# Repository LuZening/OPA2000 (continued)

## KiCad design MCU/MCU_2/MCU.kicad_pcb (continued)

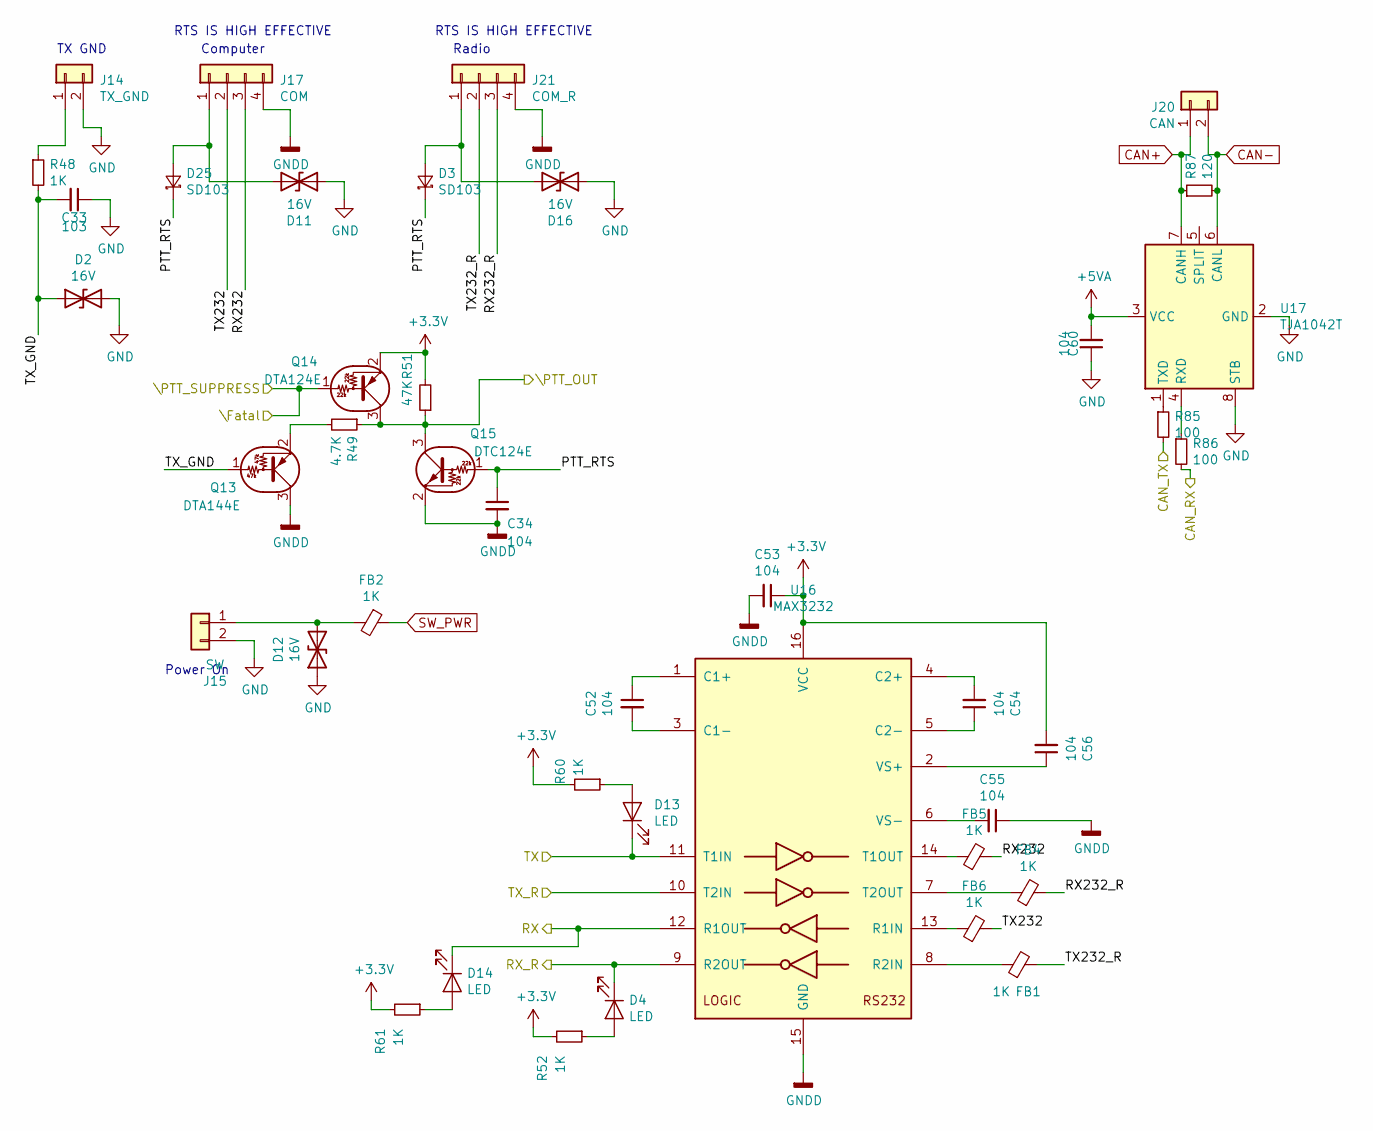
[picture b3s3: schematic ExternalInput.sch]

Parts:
C33: 103; 0805_C
C34, C52, C53, C54, C55, C56, C60: 104; 0805_C
D2, D11, D12, D16: 16V; SMA(DO-214AC)_S4
D3, D25: SD103; SOD-123
D4, D13, D14: LED; 0805_LED_S1
FB1, FB2, FB4, FB5, FB6: 1K; 0805_R
J14: TX_GND; PinHeader_1x02_P2.54mm_Vertical
J15: SW; PinHeader_1x02_P2.54mm_Vertical
J17: COM; JST_PH_B4B-PH-SM4-TB_1x04-1MP_P2.00mm_Vertical
J20: CAN; PinHeader_1x02_P2.54mm_Vertical
J21: COM_R; JST_PH_B4B-PH-SM4-TB_1x04-1MP_P2.00mm_Vertical
Q13: DTA144E; SOT-23(SOT-23-3)
Q14: DTA124E; SOT-23(SOT-23-3)
Q15: DTC124E; SOT-23(SOT-23-3)
R48, R52, R60, R61: 1K; 0805_R
R49: 4.7K; 0805_R
R51: 47K; 0805_R
R85, R86: 100; 0805_R
R87: 120; 0805_R
U16: MAX3232; SOIC-16_150MIL
U17: TJA1042T; SOIC-8_150MIL

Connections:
+3V3: C53.1, C56.2, Q14.2 (E), R51.2, R52.2, R60.2, R61.2, U16.16 (VCC); also elsewhere on the board
/CAN_RX: R86.2; also elsewhere on the board
/CAN_TX: R85.2; also elsewhere on the board
/ExternalInput/PTT_RTS: C34.1, D3.2 (K), D25.2 (K), Q15.1 (B)
/ExternalInput/RX232: FB5.2, J17.3
/ExternalInput/RX232_R: FB4.2, J21.3
/ExternalInput/TX232: FB6.2, J17.2
/ExternalInput/TX232_R: FB1.2, J21.2
/ExternalInput/TX_GND: C33.2, D2.1 (A1), Q13.1 (B), R48.2
/RX: D14.K, U16.12 (R1OUT); also elsewhere on the board
/RX3: D4.K, U16.9 (R2OUT); also elsewhere on the board
/TX: D13.K, U16.11 (T1IN); also elsewhere on the board
/TX3: U16.10 (T2IN); also elsewhere on the board
CAN+: J20.1, R87.1, U17.7 (CANH)
CAN-: J20.2, R87.2, U17.6 (CANL)
GND: C33.1, C34.2, C53.2, C55.1, C60.1, D2.2 (A2), D11.1 (A1), D12.1 (A1), D16.1 (A1), J14.2, J15.2, J17.4, J21.4, Q13.3 (C), Q15.2 (E), U16.15 (GND), U17.2 (GND), U17.8 (STB); also elsewhere on the board
unnamed: C52.1, U16.1 (C1+)
unnamed: C52.2, U16.3 (C1-)
unnamed: C54.1, U16.5 (C2-)
unnamed: C54.2, U16.4 (C2+)
unnamed: C55.2, U16.6 (VS-)
unnamed: C56.1, U16.2 (VS+)
unnamed: D4.A, R52.1
unnamed: D11.2 (A2), D25.1 (A), J17.1
unnamed: D12.2 (A2), FB2.2, J15.1
unnamed: D13.A, R60.1
unnamed: D14.A, R61.1
unnamed: D3.1 (A), D16.2 (A2), J21.1
unnamed: FB1.1, U16.8 (R2IN)
unnamed: FB4.1, U16.7 (T2OUT)
unnamed: FB5.1, U16.14 (T1OUT)
unnamed: FB6.1, U16.13 (R1IN)
unnamed: J14.1, R48.1
unnamed: Q13.2 (E), R49.2
unnamed: R85.1, U17.1 (TXD)
unnamed: R86.1, U17.4 (RXD)
SW_PWR: FB2.1
\Fatal: Q14.1 (B); also elsewhere on the board
\PTT: Q14.3 (C), Q15.3 (C), R49.1, R51.1; also elsewhere on the board

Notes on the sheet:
Power On
TX GND
Computer
RTS IS HIGH EFFECTIVE
Radio

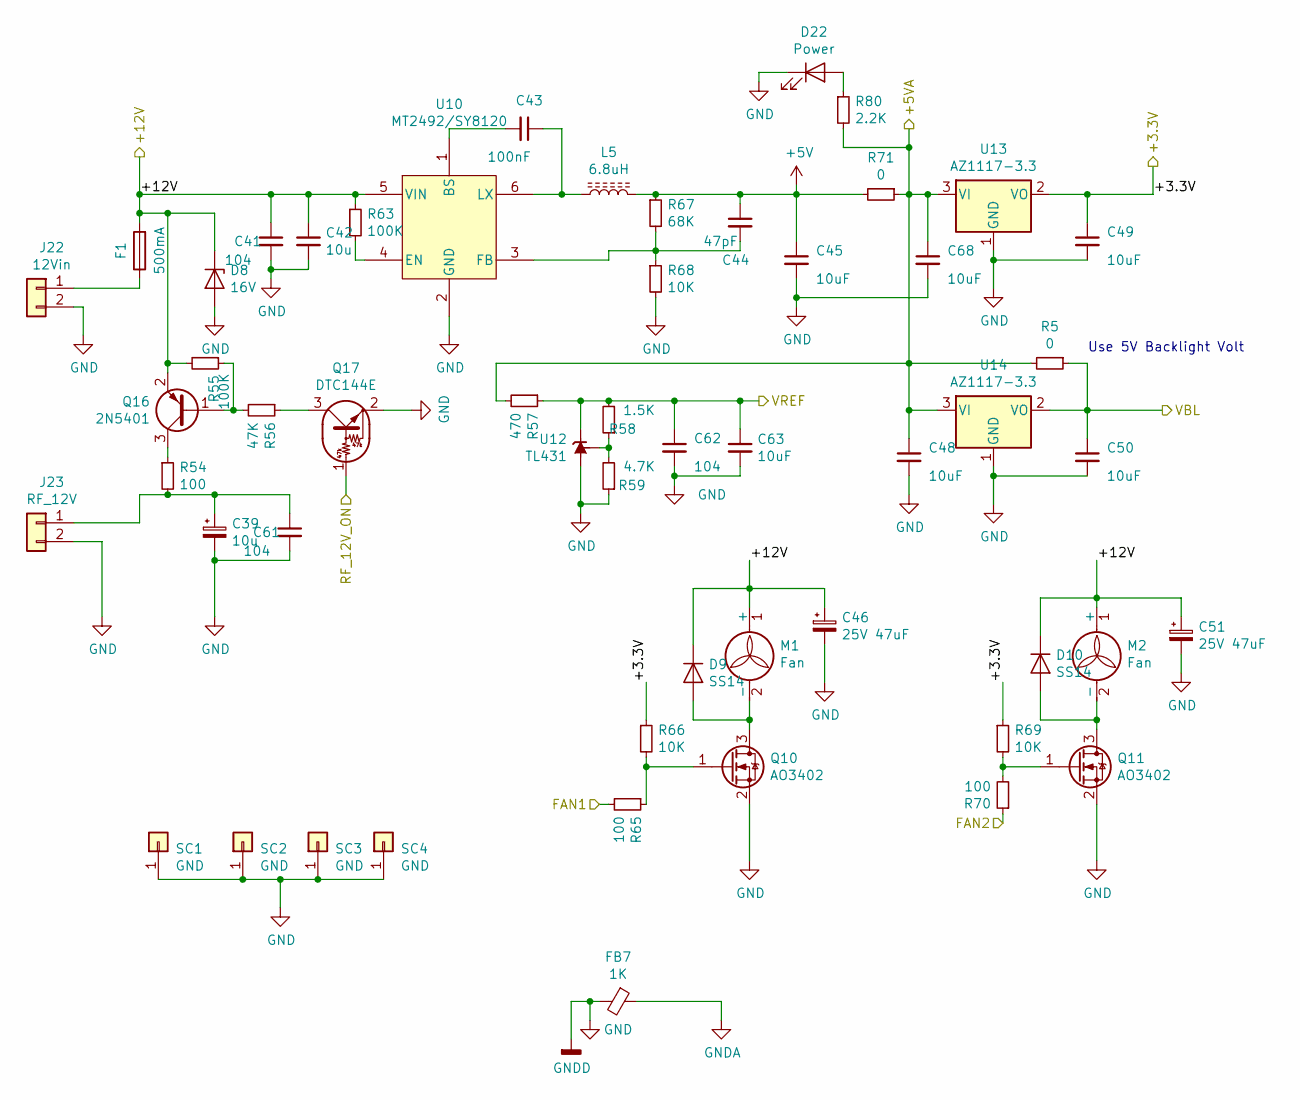
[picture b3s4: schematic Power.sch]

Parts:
C39: 10u; CP_Radial_D5.0mm_P2.50mm
C41, C61, C62: 104; 0805_C
C42: 10u; 0805_C
C43: 100nF; 0805_C
C44: 47pF; 0805_C
C45, C48, C49, C50, C63, C68: 10uF; 0805_C
C46, C51: 25V 47uF; CP_Radial_D5.0mm_P2.50mm
D8: 16V; LL-34
D9, D10: SS14; SMA(DO-214AC)_S1
D22: Power; 0805_LED_S1
F1: 500mA; 1206_R
FB7: 1K; 0201_R
J22: 12Vin; JST_PH_B2B-PH-SM4-TB_1x02-1MP_P2.00mm_Vertical
J23: RF_12V; JST_PH_B2B-PH-SM4-TB_1x02-1MP_P2.00mm_Vertical
L5: 6.8uH; L_SMD4030_hand
M1, M2: Fan; JST_PH_B2B-PH-SM4-TB_1x02-1MP_P2.00mm_Vertical
Q10, Q11: AO3402; SOT-23(SOT-23-3)
Q16: 2N5401; SOT-23(SOT-23-3)
Q17: DTC144E; SOT-23(SOT-23-3)
R5: 0; 0603_R
R54, R65, R70: 100; 0805_R
R55, R63: 100K; 0805_R
R56: 47K; 0805_R
R57: 470; 0805_R
R58: 1.5K; 0805_R
R59: 4.7K; 0805_R
R66, R68, R69: 10K; 0805_R
R67: 68K; 0805_R
R71: 0; 1206_R
R80: 2.2K; 0805_R
SC1, SC2, SC3, SC4: GND; M3_Screwhole
U10: MT2492/SY8120; SOT-23-6
U12: TL431; SOT-23(SOT-23-3)
U13, U14: AZ1117-3.3; SOT-223

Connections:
+3V3: C49.1, R66.1, R69.1, U13.2 (VO); also elsewhere on the board
+5V: C44.1, C45.1, L5.2, R67.1, R71.2
+12V: C41.1, C42.1, C46.1, C51.1, D8.2 (K), D9.2 (K), D10.2 (K), F1.2, M1.1 (+), M2.1 (+), Q16.2 (E), R55.2, R63.1, U10.5 (VIN); also elsewhere on the board
FAN1: R65.2; also elsewhere on the board
FAN2: R70.1; also elsewhere on the board
GND: C39.2, C41.2, C42.2, C45.2, C46.2, C48.2, C49.2, C50.2, C51.2, C61.2, C62.2, C63.2, C68.2, D8.1 (A), D22.K, FB7.2, J22.2, J23.2, Q10.2 (S), Q11.2 (S), Q17.2 (E), R59.1, R68.2, SC1.1, SC2.1, SC3.1, SC4.1, U10.2 (GND), U12.3 (A), U12.6 (A), U12.7 (A), U13.1 (GND), U14.1 (GND); also elsewhere on the board
GNDA: FB7.1; also elsewhere on the board
unnamed: C39.1, C61.1, J23.1, R54.2
unnamed: C43.1, L5.1, U10.6 (LX)
unnamed: C43.2, U10.1 (BS)
unnamed: C44.2, R67.2, R68.1, U10.3 (FB)
unnamed: D9.1 (A), M1.2 (-), Q10.3 (D)
unnamed: D10.1 (A), M2.2 (-), Q11.3 (D)
unnamed: D22.A, R80.1
unnamed: F1.1, J22.1
unnamed: Q10.1 (G), R65.1, R66.2
unnamed: Q11.1 (G), R69.2, R70.2
unnamed: Q16.1 (B), R55.1, R56.2
unnamed: Q16.3 (C), R54.1
unnamed: Q17.3 (C), R56.1
unnamed: R58.1, R59.2, U12.1 (REF)
unnamed: R63.2, U10.4 (EN)
RF_12V_ON: Q17.1 (B)
VBL: C50.1, R5.1, U14.2 (VO); also elsewhere on the board
VREF: C62.1, C63.1, R57.1, R58.2, U12.2 (K); also elsewhere on the board

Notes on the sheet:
Use 5V Backlight Volt

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
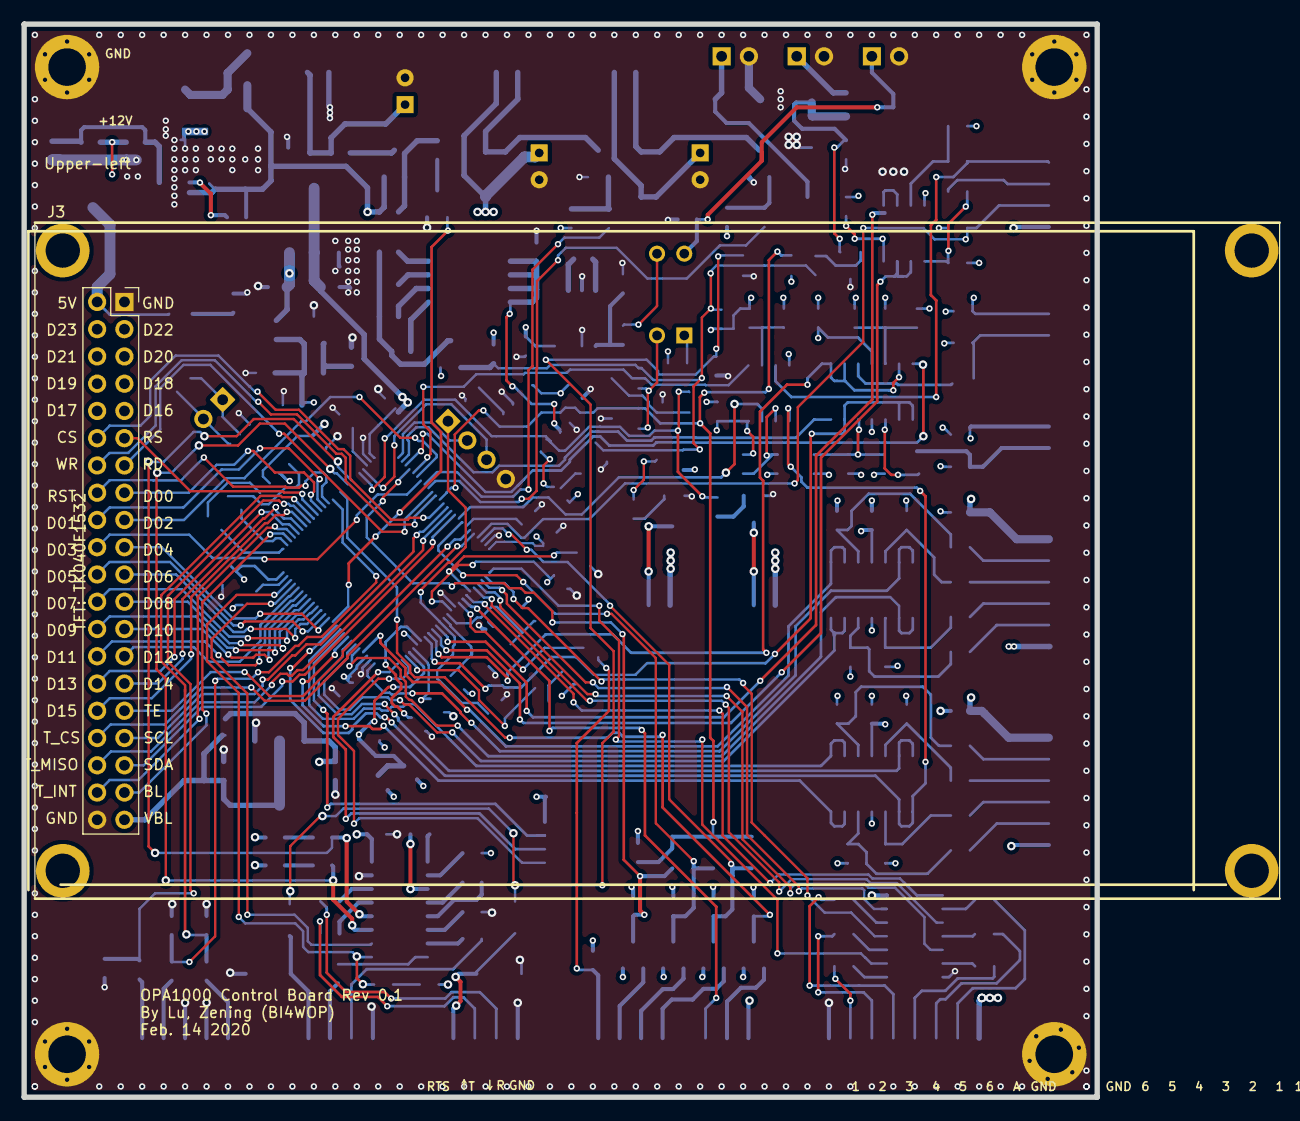
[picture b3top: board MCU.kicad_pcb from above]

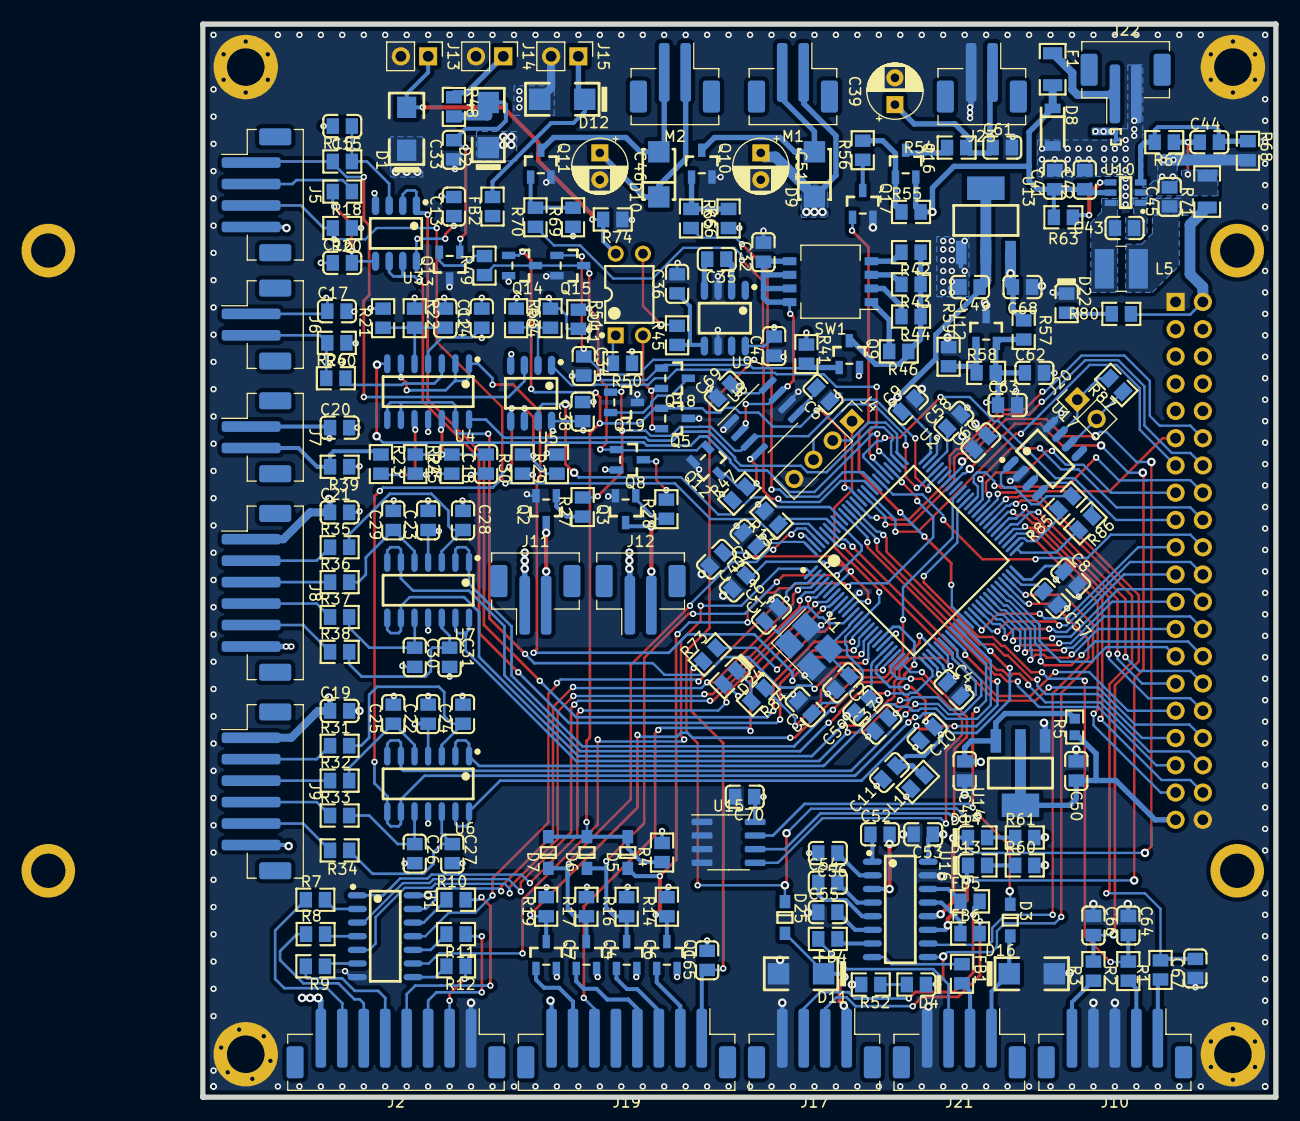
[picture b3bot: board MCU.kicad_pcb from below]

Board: 4 copper layers, 100.0 x 100.0 mm, 237 parts (236 on the bottom side), 205 nets.

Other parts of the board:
C5, C47, C69: 104; 0805_C
C32: 1uF; 0805_C
C35, C36: 10uF; 0805_C
D1: 16V; SMAF_S4
J11: In Relay; JST_PH_B2B-PH-SM4-TB_1x02-1MP_P2.00mm_Vertical
J12: Out Relay; JST_PH_B2B-PH-SM4-TB_1x02-1MP_P2.00mm_Vertical
J13: ALC out; PinHeader_1x02_P2.54mm_Vertical
Q2, Q3: 8050; SOT-23(SOT-23-3)
Q5, Q8, Q9, Q18, Q19: DTA144E; SOT-23(SOT-23-3)
Q12: DTC144E; SOT-23(SOT-23-3)
R27, R28, R41, R74: 10K; 0805_R
R42, R43, R44, R46: 51K; 0805_R
R45: 1K; 0805_R
R47: 100K; 0805_R
R50: 220; 0805_R
SW1: SW_DIP_x04; SW_DIP_SPSTx04_Slide_KingTek_DSHP04TS_W7.62mm_P1.27mm
U8: TLC555xD; SOIC-8_3.9x4.9mm_P1.27mm
U9: ICL7660; SOIC-8_150MIL
U11: PC817; DIP-4

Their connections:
+3V3: C47.2, C69.2, Q8.2, Q9.2, R41.1, R47.1, R50.1, U8.8, U9.8; also elsewhere on the board
+12V: J11.1, J12.1; also elsewhere on the board
/OutputSignals/REL_IN: J11.2, Q2.3
/OutputSignals/REL_OUT: J12.2, Q3.3
ALC: D1.1, J13.1, R74.2, U11.4
GND: C5.1, C32.2, C36.1, C47.1, C69.1, D1.2, J13.2, Q2.2, Q3.2, Q5.3, Q12.2, Q19.3, R74.1, U8.1, U8.6, U9.3, U9.6; also elsewhere on the board
unnamed: C5.2, U8.5
unnamed: C32.1, SW1.5, SW1.6, SW1.7, SW1.8, U8.2, U8.7
unnamed: C35.1, U9.2
unnamed: C35.2, U9.4
unnamed: C36.2, R45.2, U9.5
unnamed: Q2.1, R27.1
unnamed: Q3.1, R28.1
unnamed: Q8.3, R28.2
unnamed: Q9.3, R42.1, R43.1, R44.1, R46.1
unnamed: Q12.3, R47.2, U8.4
unnamed: Q5.2, Q18.2, U11.2
unnamed: Q18.3, Q19.2
unnamed: R42.2, SW1.4
unnamed: R43.2, SW1.3
unnamed: R44.2, SW1.2
unnamed: R45.1, U11.3
unnamed: R46.2, SW1.1
unnamed: R50.2, U11.1
Transmit: Q19.1, R27.2, U8.3; also elsewhere on the board
\Fatal: Q5.1; also elsewhere on the board
\PTT: Q8.1, Q9.1, Q12.1, Q18.1, R41.2; also elsewhere on the board

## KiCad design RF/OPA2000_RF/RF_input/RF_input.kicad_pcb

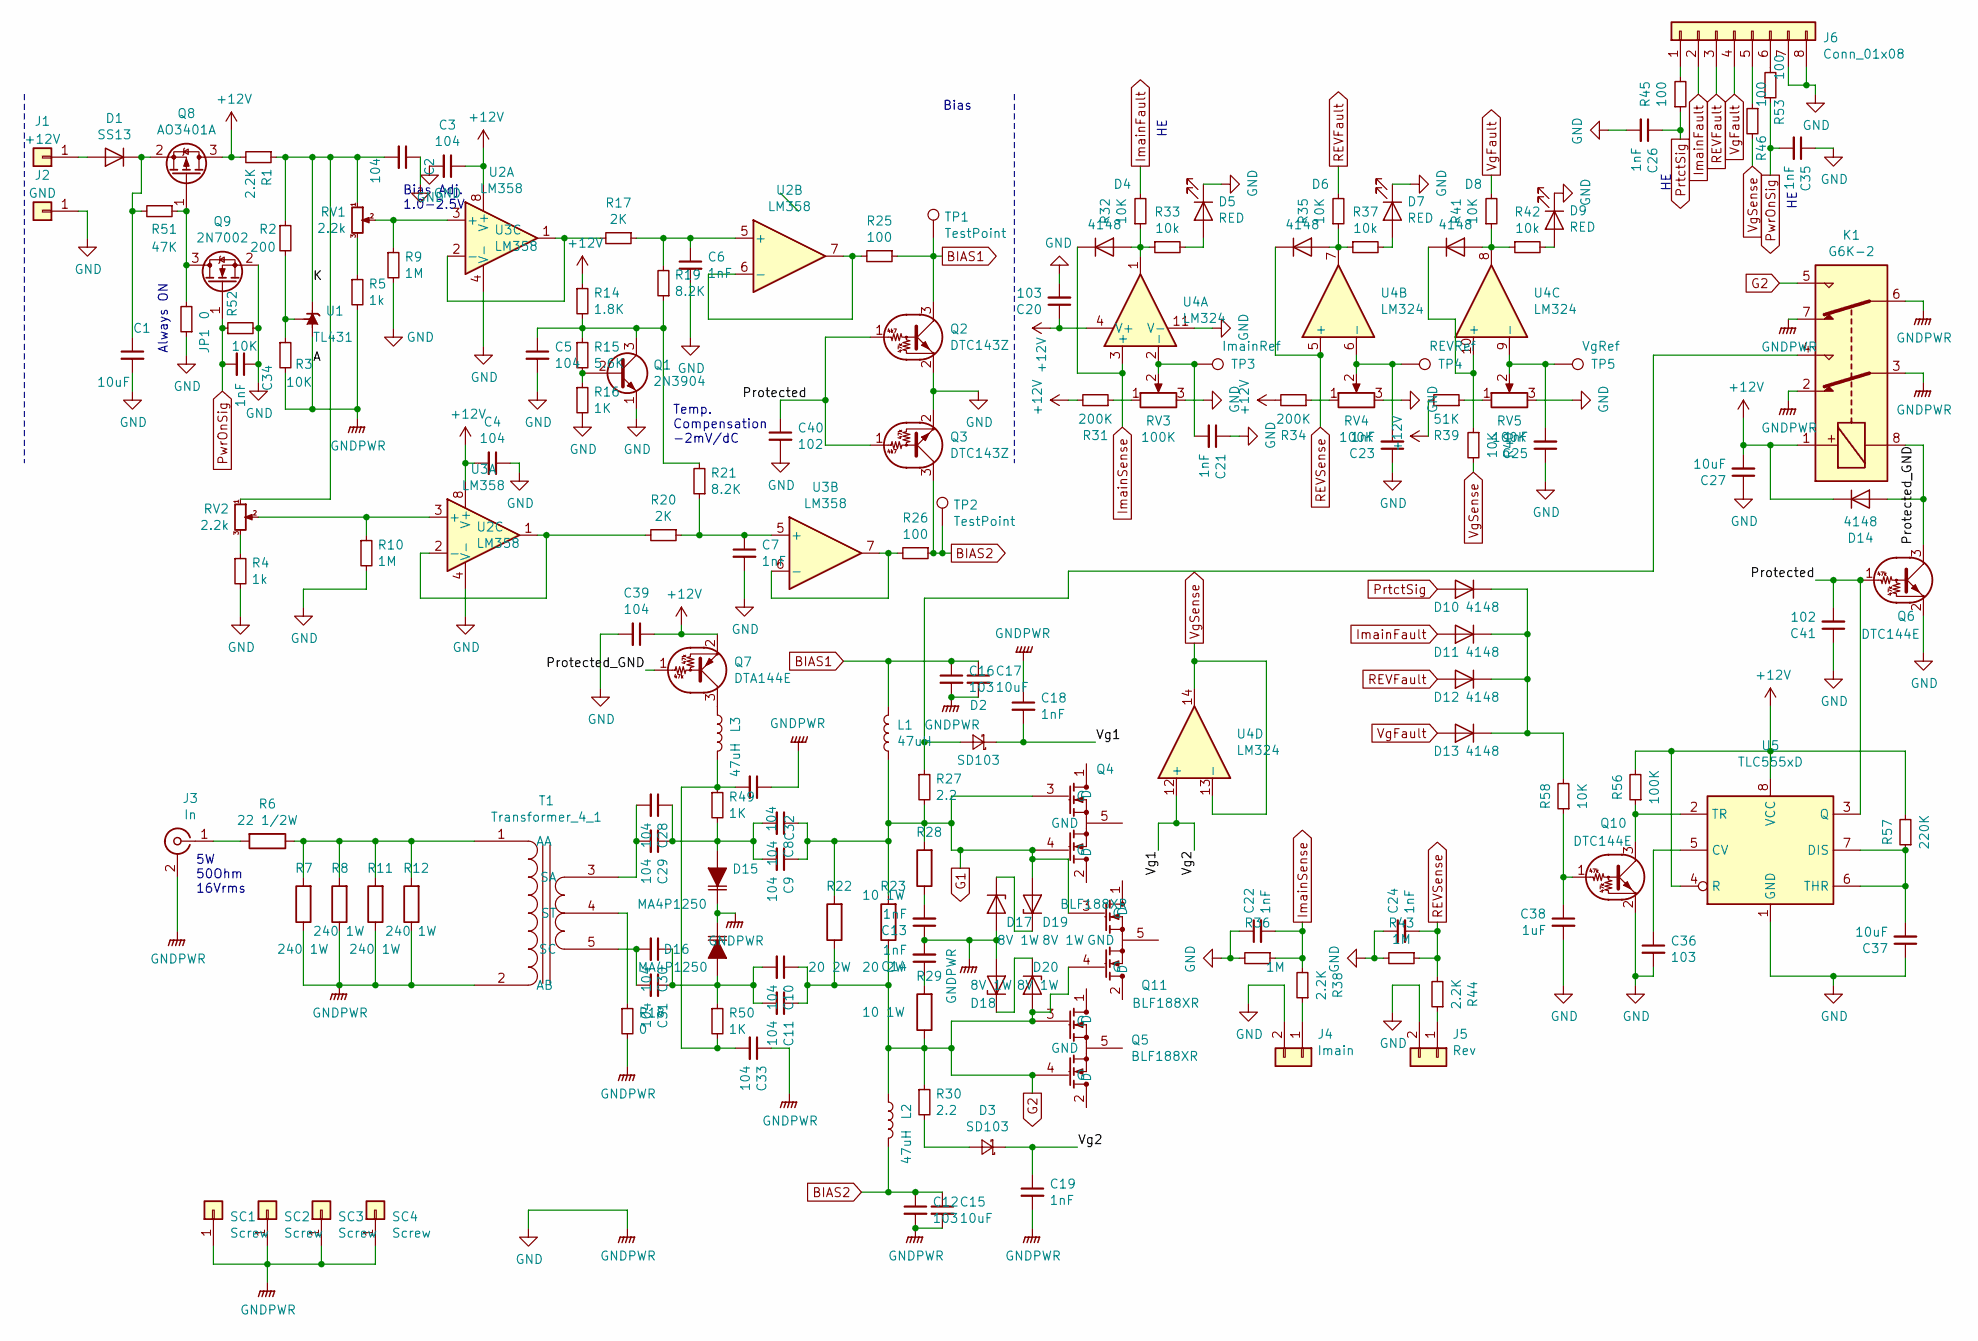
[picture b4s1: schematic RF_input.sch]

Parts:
C1: 10uF; 1206_C
C2, C3, C4, C5, C8, C9, C10, C11, C28, C29, C30, C31, C32, C33, C39: 104; 0805_C
C6, C7, C18, C19, C21, C22, C23, C24, C25, C26, C34, C35: 1nF; 0805_C
C12, C16, C20, C36: 103; 0805_C
C13, C14: 1nF; 1206_C
C15, C17, C27, C37: 10uF; 0805_C
C38: 1uF; 0805_C
C40, C41: 102; 0805_C
D1: SS13; SOD-123
D2, D3: SD103; SOD-123
D4, D6, D8, D10, D11, D12, D13, D14: 4148; SOD-123
D5, D7, D9: RED; 0805_LED
D15, D16: MA4P1250
D17, D18, D19, D20: 8V 1W; SMA(DO-214AC)_S5
J1: +12V; PCB-35-M3
J2: GND; PCB-35-M3
J3: In; RF_conn_pad
J4: Imain; JST_PH_B2B-PH-SM4-TB_02x2.00mm_Straight
J5: Rev; JST_PH_B2B-PH-SM4-TB_02x2.00mm_Straight
J6: Conn_01x08; JST_PH_B8B-PH-SM4-TB_08x2.00mm_Straight
JP1: 0; 0805_R
K1: G6K-2; HFD4S
L1, L2, L3: 47uH; L_Axial_0.4_SMD
Q1: 2N3904; TO-92-SMD
Q2, Q3: DTC143Z; SOT-23(SOT-23-3)
Q4, Q5, Q11: BLF188XR
Q6, Q10: DTC144E; SOT-23(SOT-23-3)
Q7: DTA144E; SOT-23(SOT-23-3)
Q8: AO3401A; SOT-23(SOT-23-3)
Q9: 2N7002; SOT-23(SOT-23-3)
R1, R38, R44: 2.2K; 0805_R
R2: 200; 0805_R
R3, R32, R35, R40, R41, R52, R58: 10K; 0805_R
R4, R5: 1k; 0805_R
R6: 22 1/2W; R_1812_HandSoldering
R7, R8, R11, R12: 240 1W; R_1812_HandSoldering
R9, R10, R36, R43: 1M; 0805_R
R14: 1.8K; 0805_R
R15: 5.6K; 0805_R
R16, R49, R50: 1K; 0805_R
R17, R20: 2K; 0805_R
R18: 0; 1206_R
R19, R21: 8.2K; 0805_R
R22, R23: 20 2W; R_1812_HandSoldering
R25, R26, R45, R46, R53: 100; 0805_R
R27: 2.2; L_Axial_0.4_SMD
R28, R29: 10 1W; R_1812_HandSoldering
R30: 2.2; 1206_R
R31, R34: 200K; 0805_R
R33, R37, R42: 10k; 0805_R
R39: 51K; 0805_R
R51: 47K; 0805_R
R56: 100K; 0805_R
R57: 220K; 0805_R
RV1, RV2: 2.2k; Potentiometer_Trimmer_Bourns_3224W
RV3, RV4, RV5: 100K; Potentiometer_Trimmer_Bourns_3224W
SC1, SC2, SC3, SC4: Screw; M3_Screwhole
T1: Transformer_4_1; 28B0562-100-1_4_UNUN
TP1, TP2: TestPoint; Measurement_Point_Round-SMD-Pad_Small
TP3: ImainRef; Measurement_Point_Round-SMD-Pad_Small
TP4: REVRef; Measurement_Point_Round-SMD-Pad_Small
TP5: VgRef; Measurement_Point_Round-SMD-Pad_Small
U1: TL431; SOT-23(SOT-23-3)
U2, U3: LM358; SOIC-8_150MIL
U4: LM324; SOIC-14_150MIL
U5: TLC555xD; SOIC-8_150MIL

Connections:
+12V: C3.1, C4.2, C20.1, C27.2, C39.1, D14.2 (K), K1.1, Q7.2 (E), Q8.3 (D), R1.2, R14.1, R31.2, R34.2, R39.2, R56.2, R57.2, U2.8 (V+), U3.8 (V+), U4.4 (V+), U5.4 (R), U5.8 (VCC)
/K: C2.2, R1.1, R2.1, RV1.1, RV2.1, U1.2 (K)
/Protected: C40.1, C41.2, Q2.1 (B), Q3.1 (B), Q6.1 (B), U5.3 (Q)
/Protected_GND: D14.1 (A), K1.8, Q6.3 (C), Q7.1 (B)
/Vg1: C18.2, C19.1, D2.2 (K), D3.2 (K), U4.12 (+)
BIAS1: C16.1, C17.1, L1.1, Q2.3 (C), R25.1, TP1.1
BIAS2: C12.1, C15.1, L2.2, Q3.3 (C), R26.1, TP2.1
G1: C8.1, C9.1, D19.1 (A), L1.2, Q4.3 (G), Q4.4 (G), Q11.3 (G), R22.2, R23.2, R27.2, R28.2
G2: C10.1, C11.1, D20.1 (A), K1.5, L2.1, Q5.3 (G), Q5.4 (G), Q11.4 (G), R22.1, R23.1, R29.1, R30.1
GND: C1.2, C2.1, C3.2, C4.1, C5.2, C6.2, C7.2, C12.2, C13.1, C14.2, C15.2, C16.2, C17.2, C18.1, C19.2, C20.2, C21.1, C22.1, C23.1, C24.1, C25.1, C26.2, C27.1, C32.1, C33.1, C34.1, C35.1, C36.2, C37.1, C38.2, C39.2, C40.2, C41.1, D5.2 (K), D7.2 (K), D9.2 (K), D15.2 (K), D16.2 (K), D17.1 (A), D18.1 (A), J2.1, J3.2 (Ext), J4.2, J5.2, J6.7, J6.8, JP1.1, K1.2, K1.3, K1.6, K1.7, Q1.1 (E), Q2.2 (E), Q3.2 (E), Q6.2 (E), Q9.2 (S), Q10.2 (E), R3.2, R4.2, R5.2, R7.1, R8.1, R9.2, R10.2, R11.1, R12.1, R16.2, R18.2, R36.2, R43.2, R52.2, RV3.3, RV4.3, RV5.3, SC1.1, SC2.1, SC3.1, SC4.1, T1.2 (AB), U1.3 (A), U1.6 (A), U1.7 (A), U2.4 (V-), U3.4 (V-), U4.11 (V-), U5.1 (GND)
ImainFault: D11.1 (A), J6.2, R32.2
ImainSense: C22.2, D4.2 (K), R36.1, R38.2, U4.3 (+)
unnamed: C1.1, D1.2 (K), Q8.2 (S), R51.2
unnamed: C5.1, Q1.3 (C), R14.2, R15.1, R19.1, R21.2
unnamed: C6.1, R17.1, R19.2, U2.5 (+)
unnamed: C7.1, R20.1, R21.1, U3.5 (+)
unnamed: C10.2, C11.2, C30.1, C31.1, D16.1 (A), R50.1
unnamed: C13.2, R28.1
unnamed: C14.1, R29.2
unnamed: C21.2, RV3.2, TP3.1, U4.2 (-)
unnamed: C23.2, RV4.2, TP4.1, U4.6 (-)
unnamed: C25.2, RV5.2, TP5.1, U4.9 (-)
unnamed: C8.2, C9.2, C28.1, C29.1, D15.1 (A), R49.2
unnamed: C28.2, C29.2, T1.3 (SA)
unnamed: C30.2, C31.2, T1.5 (SC)
unnamed: C32.2, C33.2, L3.2, R49.1, R50.2
unnamed: C36.1, U5.5 (CV)
unnamed: C37.2, R57.1, U5.6 (THR), U5.7 (DIS)
unnamed: C38.1, Q10.1 (B), R58.1
unnamed: D1.1 (A), J1.1
unnamed: D2.1 (A), K1.4, R27.1
unnamed: D3.1 (A), R30.2
unnamed: D4.1 (A), R32.1, R33.1, U4.1
unnamed: D5.1 (A), R33.2
unnamed: D6.1 (A), R35.1, R37.1, U4.7
unnamed: D7.1 (A), R37.2
unnamed: D8.1 (A), R41.1, R42.1, U4.8
unnamed: D8.2 (K), R40.1, U4.10 (+)
unnamed: D9.1 (A), R42.2
unnamed: D10.2 (K), D11.2 (K), D12.2 (K), D13.2 (K), R58.2
unnamed: D17.2 (K), D19.2 (K)
unnamed: D18.2 (K), D20.2 (K)
unnamed: J3.1 (In), R6.2
unnamed: J4.1, R38.1
unnamed: J5.1, R44.1
unnamed: J6.1, R45.2
unnamed: J6.5, R46.1
unnamed: J6.6, R53.2
unnamed: JP1.2, Q8.1 (G), Q9.3 (D), R51.1
unnamed: L3.1, Q7.3 (C)
unnamed: Q1.2 (B), R15.2, R16.1
unnamed: Q10.3 (C), R56.1, U5.2 (TR)
unnamed: R2.2, R3.1, U1.1 (REF)
unnamed: R4.1, RV2.3
unnamed: R5.1, RV1.3
unnamed: R9.1, RV1.2, U2.3 (+)
unnamed: R10.1, RV2.2, U3.3 (+)
unnamed: R6.1, R7.2, R8.2, R11.2, R12.2, T1.1 (AA)
unnamed: R17.2, U2.1, U2.2 (-)
unnamed: R18.1, T1.4 (ST)
unnamed: R20.2, U3.1, U3.2 (-)
unnamed: R25.2, U2.6 (-), U2.7
unnamed: R26.2, U3.6 (-), U3.7
unnamed: R31.1, RV3.1
unnamed: R34.1, RV4.1
unnamed: R39.1, RV5.1
PrtctSig: C26.1, D10.1 (A), R45.1
PwrOnSig: C34.2, C35.2, Q9.1 (G), R52.1, R53.1
REVFault: D12.1 (A), J6.3, R35.2
REVSense: C24.2, D6.2 (K), R43.1, R44.2, U4.5 (+)
VgFault: D13.1 (A), J6.4, R41.2
VgSense: R40.2, R46.2, U4.13 (-), U4.14

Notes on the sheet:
Temp. Compensation -2mV/dC
Bias Adj. 1.0-2.5V
Bias
5W 50Ohm 16Vrms
Always ON

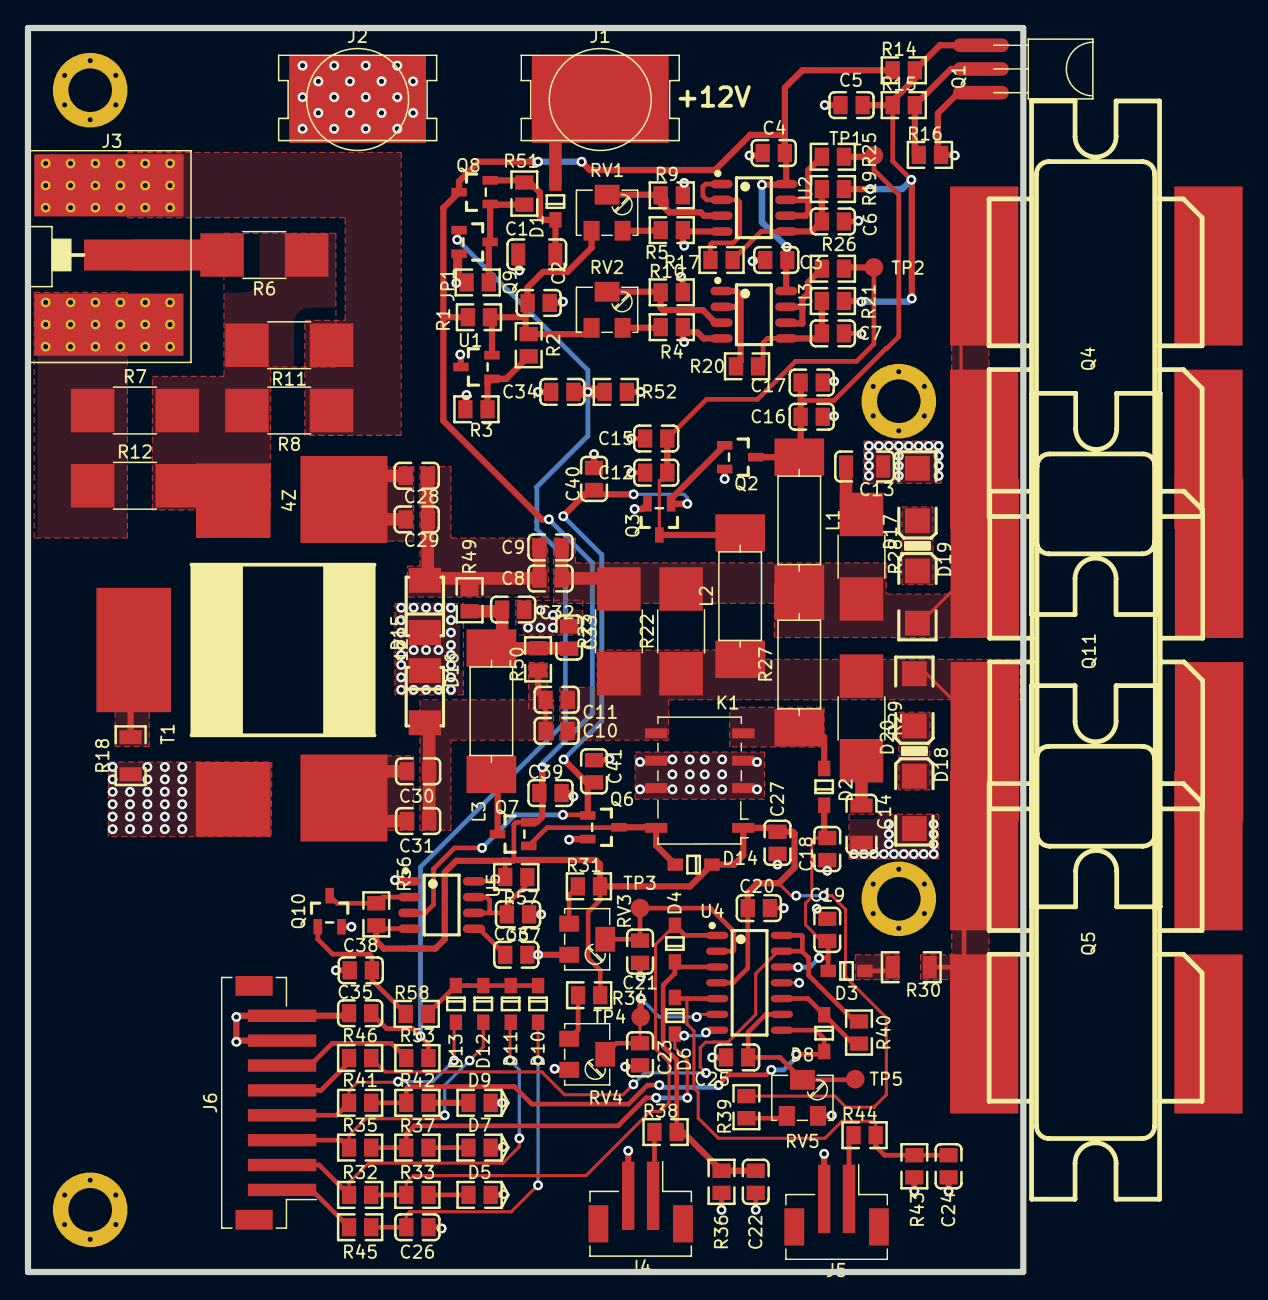
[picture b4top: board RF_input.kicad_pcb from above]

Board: 4 copper layers, 80.0 x 100.0 mm, 155 parts (0 on the bottom side), 72 nets.

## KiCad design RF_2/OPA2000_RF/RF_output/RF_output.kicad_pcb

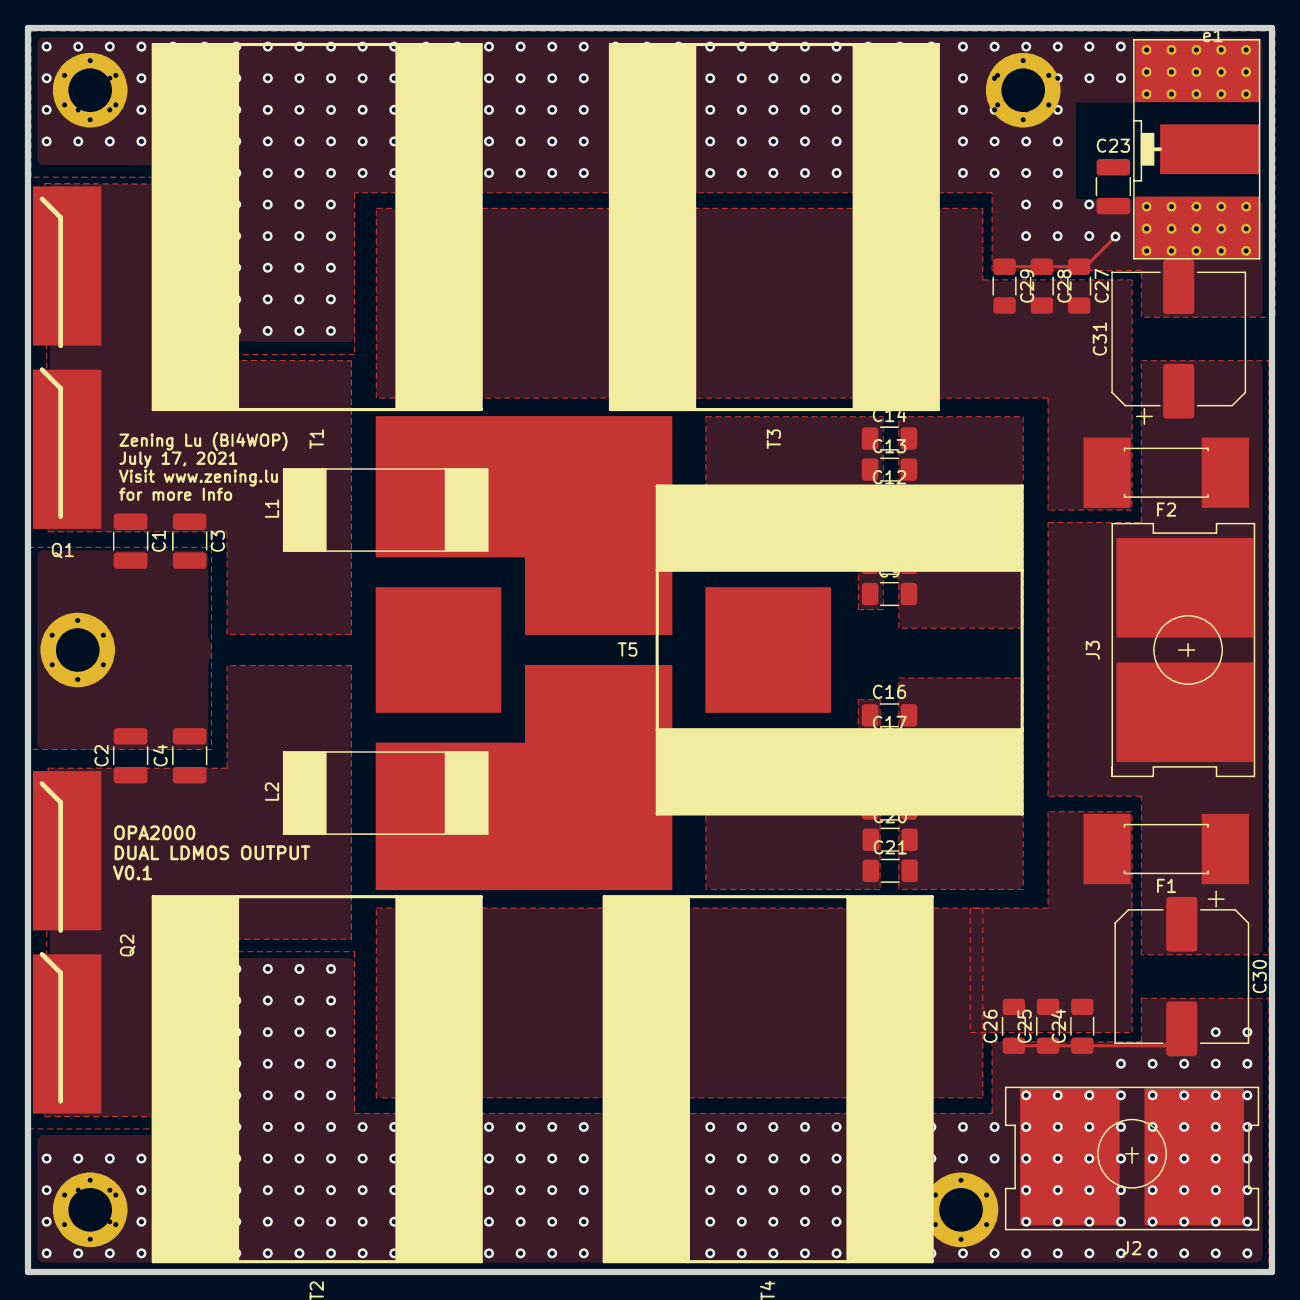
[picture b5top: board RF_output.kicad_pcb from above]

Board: 2 copper layers, 100.0 x 100.0 mm, 44 parts (0 on the bottom side), 11 nets.

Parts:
C1, C2, C3, C4: 120pF; C_1210_3225Metric_Pad1.33x2.70mm_HandSolder
C9, C10, C11, C12, C13, C14, C16, C17, C18, C19, C20, C21, C24, C25, C26, C27, C28, C29: 103; C_1206_3216Metric_Pad1.33x1.80mm_HandSolder
C23: 30pF; C_1210_3225Metric_Pad1.33x2.70mm_HandSolder
C30, C31: 220uF 100V; CP_Elec_10x10.5
F1, F2: 30A; Fuseholder_Littelfuse_Nano2_456
J2: GND; PCB-10B-M4
J3: VDD in; PCB-10B-M4
L1, L2: Choke; 5943004901
Q1, Q2: BLF188XR
SC1, SC2, SC3, SC4, SC5: GND; M3_Screwhole
T1, T2, T3, T4, T5: TLT; Laird_28B1020_100
e1: Conn_Coaxial; RF_conn_pad_short

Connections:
GNDPWR: C1.2, C2.2, C3.2, C4.2, C23.2, C24.1, C25.1, C26.1, C27.1, C28.1, C29.1, C30.2, C31.2, J2.1, SC1.1, SC2.1, SC3.1, SC4.1, SC5.1, e1.2
unnamed: C1.1, C3.1, Q1.1, Q1.2
unnamed: C2.1, C4.1, Q2.1, Q2.2
unnamed: C9.1, C10.1, C11.1, C12.1, C13.1, C14.1
unnamed: C9.2, C10.2, C11.2, C12.2, C13.2, C14.2
unnamed: C16.1, C17.1, C18.1, C19.1, C20.1, C21.1
unnamed: C16.2, C17.2, C18.2, C19.2, C20.2, C21.2
unnamed: C23.1, e1.1
unnamed: C24.2, C25.2, C26.2, F1.2
unnamed: C27.2, C28.2, C29.2, F2.2
VDD: C30.1, C31.1, F1.1, F2.1, J3.1

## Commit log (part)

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2021-04-29 First submission
2021-10-05 MCU2 sch done
2021-10-08 MCU PCB start layouting
2021-10-24 routing signals
2021-11-13 almost finished routing MCU2
2021-11-30 added EEPROM to MCU
